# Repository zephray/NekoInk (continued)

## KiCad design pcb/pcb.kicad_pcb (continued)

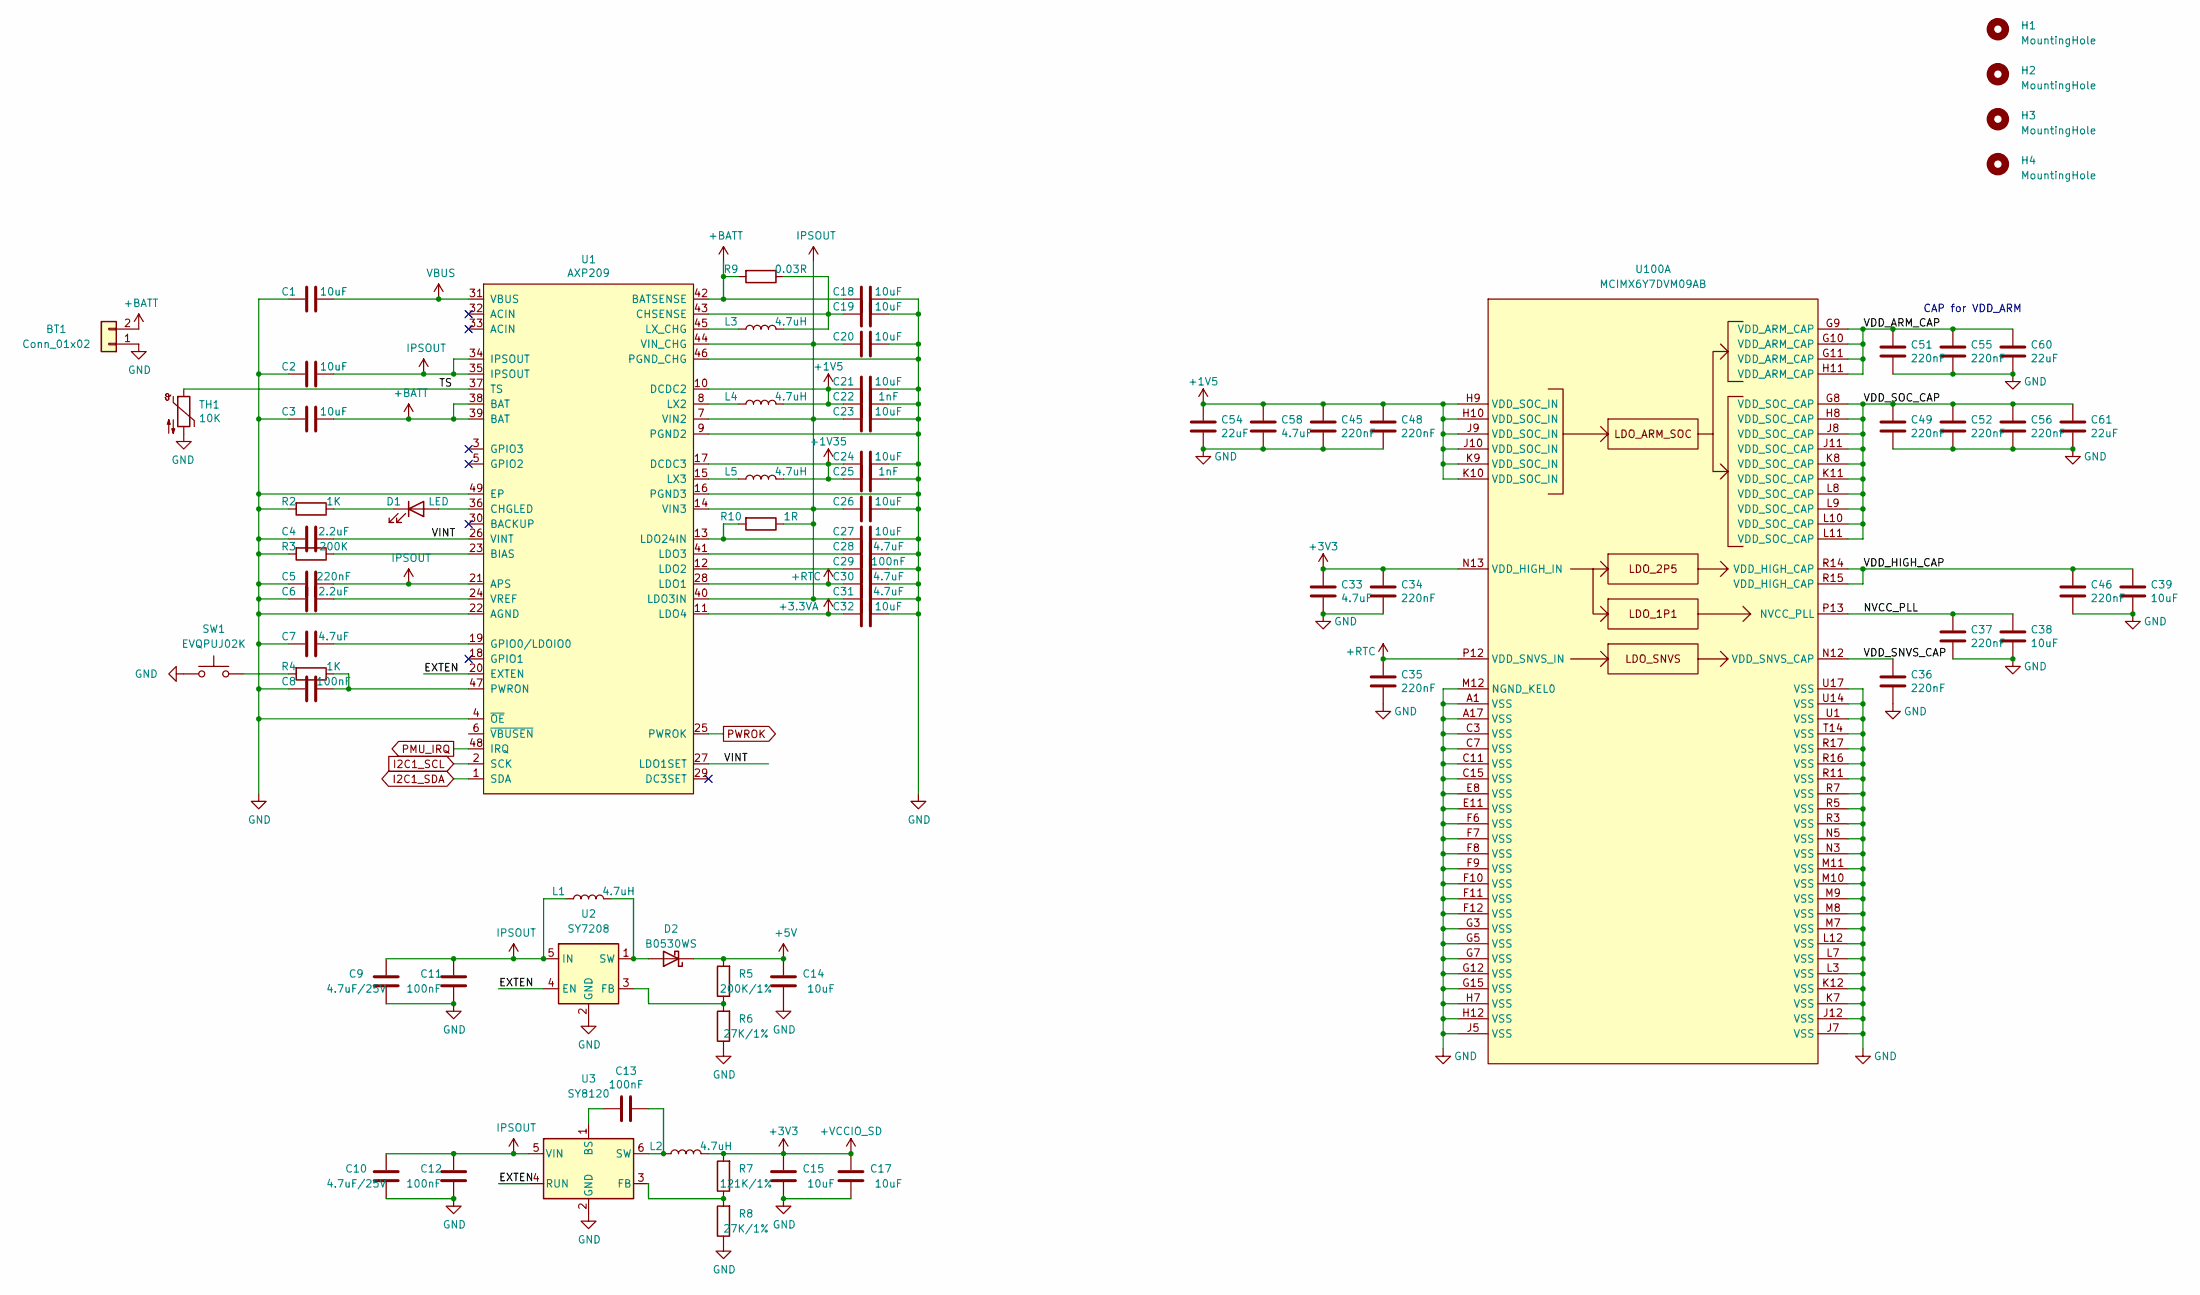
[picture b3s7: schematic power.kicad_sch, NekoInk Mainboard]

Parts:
BT1: Conn_01x02; Molex_PicoBlade_53261-0271_1x02-1MP_P1.25mm_Horizontal
C1, C2, C3, C14, C15, C17, C18, C19, C20, C21, C23, C24, C26, C27, C32, C38, C39: 10uF; C_0603_1608Metric
C4, C6: 2.2uF; C_0402_1005Metric
C5, C34, C35, C36, C37, C45, C46, C48, C49, C51, C52, C55, C56: 220nF; C_0402_1005Metric
C7, C28, C30, C31, C33, C58: 4.7uF; C_0603_1608Metric
C8, C11, C12, C13, C29: 100nF; C_0402_1005Metric
C9, C10: 4.7uF/25V; C_0805_2012Metric
C22, C25: 1nF; C_0402_1005Metric
C54, C60, C61: 22uF; C_0603_1608Metric
D1: LED; D_0603_1608Metric
D2: B0530WS; D_SOD-323
H1, H2, H3, H4: MountingHole; MountingHole_2.2mm_M2_DIN965
L1, L2, L3, L4, L5: 4.7uH; L_1212
R2, R4: 1K; R_0402_1005Metric
R3: 200K; R_0402_1005Metric
R5: 200K/1%; R_0402_1005Metric
R6, R8: 27K/1%; R_0402_1005Metric
R7: 121K/1%; R_0402_1005Metric
R9: 0.03R; R_0805_2012Metric
R10: 1R; R_0603_1608Metric
SW1: EVQPUJ02K; Panasonic_EVQPUJ_EVQPUA
TH1: 10K; R_0603_1608Metric
U1: AXP209; QFN-48-1EP_6x6mm_P0.4mm_EP4.2x4.2mm_ThermalVias
U2: SY7208; SOT-23-6
U3: SY8120; TSOT-23-6
U100: MCIMX6Y7DVM09AB; BGA-289_17x17_14.0x14.0mm

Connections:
+1V5: C21.2, C22.2, C45.1, C48.1, C54.1, C58.1, L4.2, U1.10 (DCDC2), U100.H9 (VDD_SOC_IN), U100.H10 (VDD_SOC_IN), U100.J9 (VDD_SOC_IN), U100.J10 (VDD_SOC_IN), U100.K9 (VDD_SOC_IN), U100.K10 (VDD_SOC_IN)
+1V35: C24.2, C25.2, L5.2, U1.17 (DCDC3); also elsewhere on the board
+3.3VA: C32.2, U1.11 (LDO4)
+5V: C14.2, D2.1 (K), R5.2; also elsewhere on the board
+BATT: BT1.2, C3.1, C18.2, R9.2, U1.38 (BAT), U1.39 (BAT), U1.42 (BATSENSE)
+RTC: C30.2, C35.1, U1.28 (LDO1), U100.P12 (VDD_SNVS_IN); also elsewhere on the board
/power/EXTEN: U1.20 (EXTEN), U2.4 (EN), U3.4 (RUN)
/power/NVCC_PLL: C37.1, C38.1, U100.P13 (NVCC_PLL)
/power/TS: TH1.1, U1.37 (TS)
/power/VDD_ARM_CAP: C51.1, C55.1, C60.1, U100.G9 (VDD_ARM_CAP), U100.G10 (VDD_ARM_CAP), U100.G11 (VDD_ARM_CAP), U100.H11 (VDD_ARM_CAP)
/power/VDD_HIGH_CAP: C39.1, C46.1, U100.R14 (VDD_HIGH_CAP), U100.R15 (VDD_HIGH_CAP)
/power/VDD_SNVS_CAP: C36.1, U100.N12 (VDD_SNVS_CAP)
/power/VDD_SOC_CAP: C49.1, C52.1, C56.1, C61.1, U100.G8 (VDD_SOC_CAP), U100.H8 (VDD_SOC_CAP), U100.J8 (VDD_SOC_CAP), U100.J11 (VDD_SOC_CAP), U100.K8 (VDD_SOC_CAP), U100.K11 (VDD_SOC_CAP), U100.L8 (VDD_SOC_CAP), U100.L9 (VDD_SOC_CAP), U100.L10 (VDD_SOC_CAP), U100.L11 (VDD_SOC_CAP)
/power/VINT: C4.1, U1.26 (VINT), U1.27 (LDO1SET)
GND: BT1.1, C1.2, C2.2, C3.2, C4.2, C5.2, C6.2, C7.2, C8.2, C9.1, C10.1, C11.1, C12.1, C14.1, C15.1, C17.1, C18.1, C19.1, C20.1, C21.1, C22.1, C23.1, C24.1, C25.1, C26.1, C27.1, C28.1, C29.1, C30.1, C31.1, C32.1, C33.2, C34.2, C35.2, C36.2, C37.2, C38.2, C39.2, C45.2, C46.2, C48.2, C49.2, C51.2, C52.2, C54.2, C55.2, C56.2, C58.2, C60.2, C61.2, R2.2, R3.2, R6.1, R8.1, SW1.2, TH1.2, U1.4 (~OE), U1.9 (PGND2), U1.16 (PGND3), U1.22 (AGND), U1.46 (PGND_CHG), U1.49 (EP), U2.2 (GND), U3.2 (GND), U100.A1 (VSS), U100.A17 (VSS), U100.C3 (VSS), U100.C7 (VSS), U100.C11 (VSS), U100.C15 (VSS), U100.E8 (VSS), U100.E11 (VSS), U100.F6 (VSS), U100.F7 (VSS), U100.F8 (VSS), U100.F9 (VSS), U100.F10 (VSS), U100.F11 (VSS), U100.F12 (VSS), U100.G3 (VSS), U100.G5 (VSS), U100.G7 (VSS), U100.G12 (VSS), U100.G15 (VSS), U100.H7 (VSS), U100.H12 (VSS), U100.J5 (VSS), U100.J7 (VSS), U100.J12 (VSS), U100.K7 (VSS), U100.K12 (VSS), U100.L3 (VSS), U100.L7 (VSS), U100.L12 (VSS), U100.M7 (VSS), U100.M8 (VSS), U100.M9 (VSS), U100.M10 (VSS), U100.M11 (VSS), U100.M12 (NGND_KEL0), U100.N3 (VSS), U100.N5 (VSS), U100.R3 (VSS), U100.R5 (VSS), U100.R7 (VSS), U100.R11 (VSS), U100.R16 (VSS), U100.R17 (VSS), U100.T14 (VSS), U100.U1 (VSS), U100.U14 (VSS), U100.U17 (VSS); also elsewhere on the board
I2C1_SCL: U1.2 (SCK); also elsewhere on the board
I2C1_SDA: U1.1 (SDA); also elsewhere on the board
IPSOUT: C2.1, C5.1, C9.2, C10.2, C11.2, C12.2, C20.2, C23.2, C26.2, C31.2, L1.1, R10.1, U1.7 (VIN2), U1.14 (VIN3), U1.21 (APS), U1.34 (IPSOUT), U1.35 (IPSOUT), U1.40 (LDO3IN), U1.44 (VIN_CHG), U2.5 (IN), U3.5 (VIN); also elsewhere on the board
unnamed: C6.1, U1.24 (VREF)
unnamed: C7.1, U1.19 (GPIO0/LDOIO0)
unnamed: C8.1, R4.1, U1.47 (PWRON)
unnamed: C13.1, L2.1, U3.6 (SW)
unnamed: C13.2, U3.1 (BS)
unnamed: C19.2, L3.2, R9.1, U1.43 (CHSENSE)
unnamed: C27.2, R10.2, U1.13 (LDO24IN)
unnamed: C28.2, U1.41 (LDO3)
unnamed: C29.2, U1.12 (LDO2)
unnamed: D1.1 (K), R2.1
unnamed: D1.2 (A), U1.36 (CHGLED)
unnamed: D2.2 (A), L1.2, U2.1 (SW)
unnamed: L3.1, U1.45 (LX_CHG)
unnamed: L4.1, U1.8 (LX2)
unnamed: L5.1, U1.15 (LX3)
unnamed: R3.1, U1.23 (BIAS)
unnamed: R4.2, SW1.1
unnamed: R5.1, R6.2, U2.3 (FB)
unnamed: R7.1, R8.2, U3.3 (FB)
PWROK: U1.25 (PWROK); also elsewhere on the board
VBUS: C1.1, U1.31 (VBUS); also elsewhere on the board

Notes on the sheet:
CAP for VDD_ARM

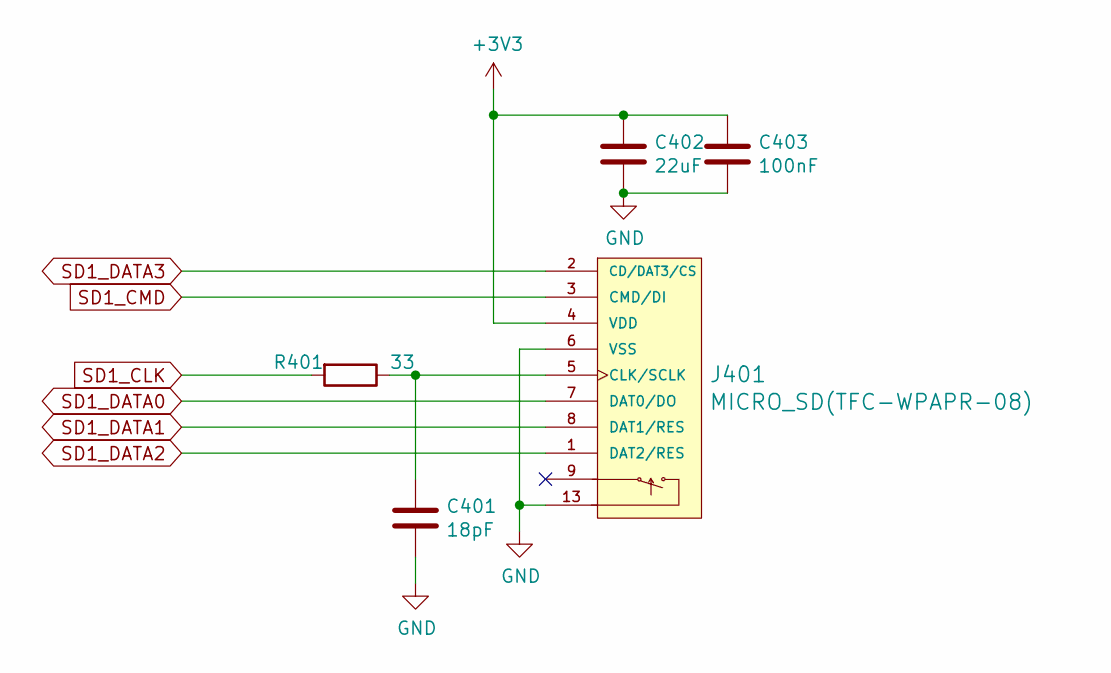
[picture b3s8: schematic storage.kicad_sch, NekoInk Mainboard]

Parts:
C401: 18pF; C_0402_1005Metric
C402: 22uF; C_0603_1608Metric
C403: 100nF; C_0402_1005Metric
J401: MICRO_SD(TFC-WPAPR-08); TFC-WPAPR-08
R401: 33; R_0402_1005Metric

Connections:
GND: C401.2, C402.2, C403.2, J401.6 (VSS), J401.10, J401.11, J401.12, J401.13; also elsewhere on the board
unnamed: C401.1, J401.5 (CLK/SCLK), R401.1
SD1_CLK: R401.2; also elsewhere on the board
SD1_CMD: J401.3 (CMD/DI); also elsewhere on the board
SD1_DATA0: J401.7 (DAT0/DO); also elsewhere on the board
SD1_DATA1: J401.8 (DAT1/RES); also elsewhere on the board
SD1_DATA2: J401.1 (DAT2/RES); also elsewhere on the board
SD1_DATA3: J401.2 (CD/DAT3/CS); also elsewhere on the board

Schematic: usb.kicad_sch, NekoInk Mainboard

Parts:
C601, C602: 10uF/25V; C_0805_2012Metric
C613, C615: 100nF; C_0402_1005Metric
J601: USB_AB_Micro; USB_Micro-AB_Molex_47590-0001
J602, J604: USB_B_Micro; USB_Micro-B_Amphenol_10103594-0001LF_Horizontal
L601, L602: EXC14CE900U; L_CommonModeChoke_Panasonic_EXC14CE
L603, L604: 120R; L_0603_1608Metric
R606, R607: 22; R_0402_1005Metric
U601, U605: USBLC6-2P6; SOT-666
U602: CP2102N-Axx-xQFN20; SiliconLabs_QFN-20-1EP_3x3mm_P0.5mm_EP1.8x1.8mm

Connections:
+5V: C601.1, L603.1; also elsewhere on the board
/usb/DEVICE_DN: J602.2 (D-), L601.4, U605.1 (I/O1), U605.6 (I/O1)
/usb/DEVICE_DP: J602.3 (D+), L601.3, U605.3 (I/O2), U605.4 (I/O2)
/usb/HOST_DN: J601.2 (D-), L602.3, U601.1 (I/O1), U601.6 (I/O1)
/usb/HOST_DP: J601.3 (D+), L602.4, U601.3 (I/O2), U601.4 (I/O2)
GND: C601.2, C602.2, C613.2, C615.2, J601.4 (ID), J601.5 (GND), J601.6 (Shield), J602.4 (ID), J602.5 (GND), J602.6 (Shield), J604.4 (ID), J604.5 (GND), J604.6 (Shield), U601.2 (GND), U602.3 (GND), U602.12 (GND), U602.21 (GND), U605.2 (GND); also elsewhere on the board
unnamed: C613.1, C615.1, U602.6 (VDD)
unnamed: J601.1 (VBUS), L603.2, U601.5 (VBUS)
unnamed: J602.1 (VBUS), L604.2, U605.5 (VBUS)
unnamed: J604.1 (VBUS), U602.7 (VREGIN), U602.8 (VBUS)
unnamed: J604.2 (D-), R607.1
unnamed: J604.3 (D+), R606.1
unnamed: R606.2, U602.4 (D+)
unnamed: R607.2, U602.5 (D-)
UART3_RXD: U602.18 (TXD); also elsewhere on the board
UART3_TXD: U602.17 (RXD); also elsewhere on the board
USB_DEVICE_DN: L601.1; also elsewhere on the board
USB_DEVICE_DP: L601.2; also elsewhere on the board
USB_HOST_DN: L602.2; also elsewhere on the board
USB_HOST_DP: L602.1; also elsewhere on the board
VBUS: C602.1, L604.1; also elsewhere on the board

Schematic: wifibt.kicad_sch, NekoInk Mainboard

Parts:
ANT901: PCB_WIFI_ANT; bt_antenna_1ant_2gnd
C901, C902: DNP; C_0402_1005Metric
C903: 33pF/50V/5%; C_0402_1005Metric
C904, C906: 100nF; C_0402_1005Metric
C905, C907: 10uF; C_0603_1608Metric
R901: 0R; R_0402_1005Metric
R902: 10K; R_0402_1005Metric
U901: RTL8723BS; RL-SM02BD(RTL8723BS)
X901: 32.768kHz; Oscillator_SMD_Abracon_ASE-4Pin_3.2x2.5mm

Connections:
GND: ANT901.2, C901.1, C902.1, C904.2, C905.2, C906.2, C907.2, U901.1 (GND), U901.20 (GND), U901.31 (GND), U901.33 (GND), U901.36 (GND), X901.2 (GND); also elsewhere on the board
unnamed: ANT901.1, C901.2, R901.2
unnamed: C902.2, C903.2, R901.1
unnamed: C903.1, U901.2 (WIFI/BT_ANT)
unnamed: R902.2, X901.1 (EN)
unnamed: U901.24 (SUSCLK_IN/GPIO6), X901.3 (OUT)
SD2_CLK: U901.17 (SD_CLK); also elsewhere on the board
SD2_CMD: U901.16 (SD_CMD); also elsewhere on the board
SD2_DATA0: U901.18 (SD_D0); also elsewhere on the board
SD2_DATA1: U901.19 (SD_D1); also elsewhere on the board
SD2_DATA2: U901.14 (SD_D2); also elsewhere on the board
SD2_DATA3: U901.15 (SD_D3); also elsewhere on the board
UART2_CTS: U901.41 (UART_RTS); also elsewhere on the board
UART2_RTS: U901.44 (UART_CTS); also elsewhere on the board
UART2_RXD: U901.42 (UART_OUT); also elsewhere on the board
UART2_TXD: U901.43 (UART_IN); also elsewhere on the board
WL_PMU_EN: U901.12 (WL_DIS#/GPIO9); also elsewhere on the board
WL_WAKE_AP: U901.13 (WL_HOST_WAKE); also elsewhere on the board

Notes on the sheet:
Headset profile is not supported. Use A2DP instead.

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
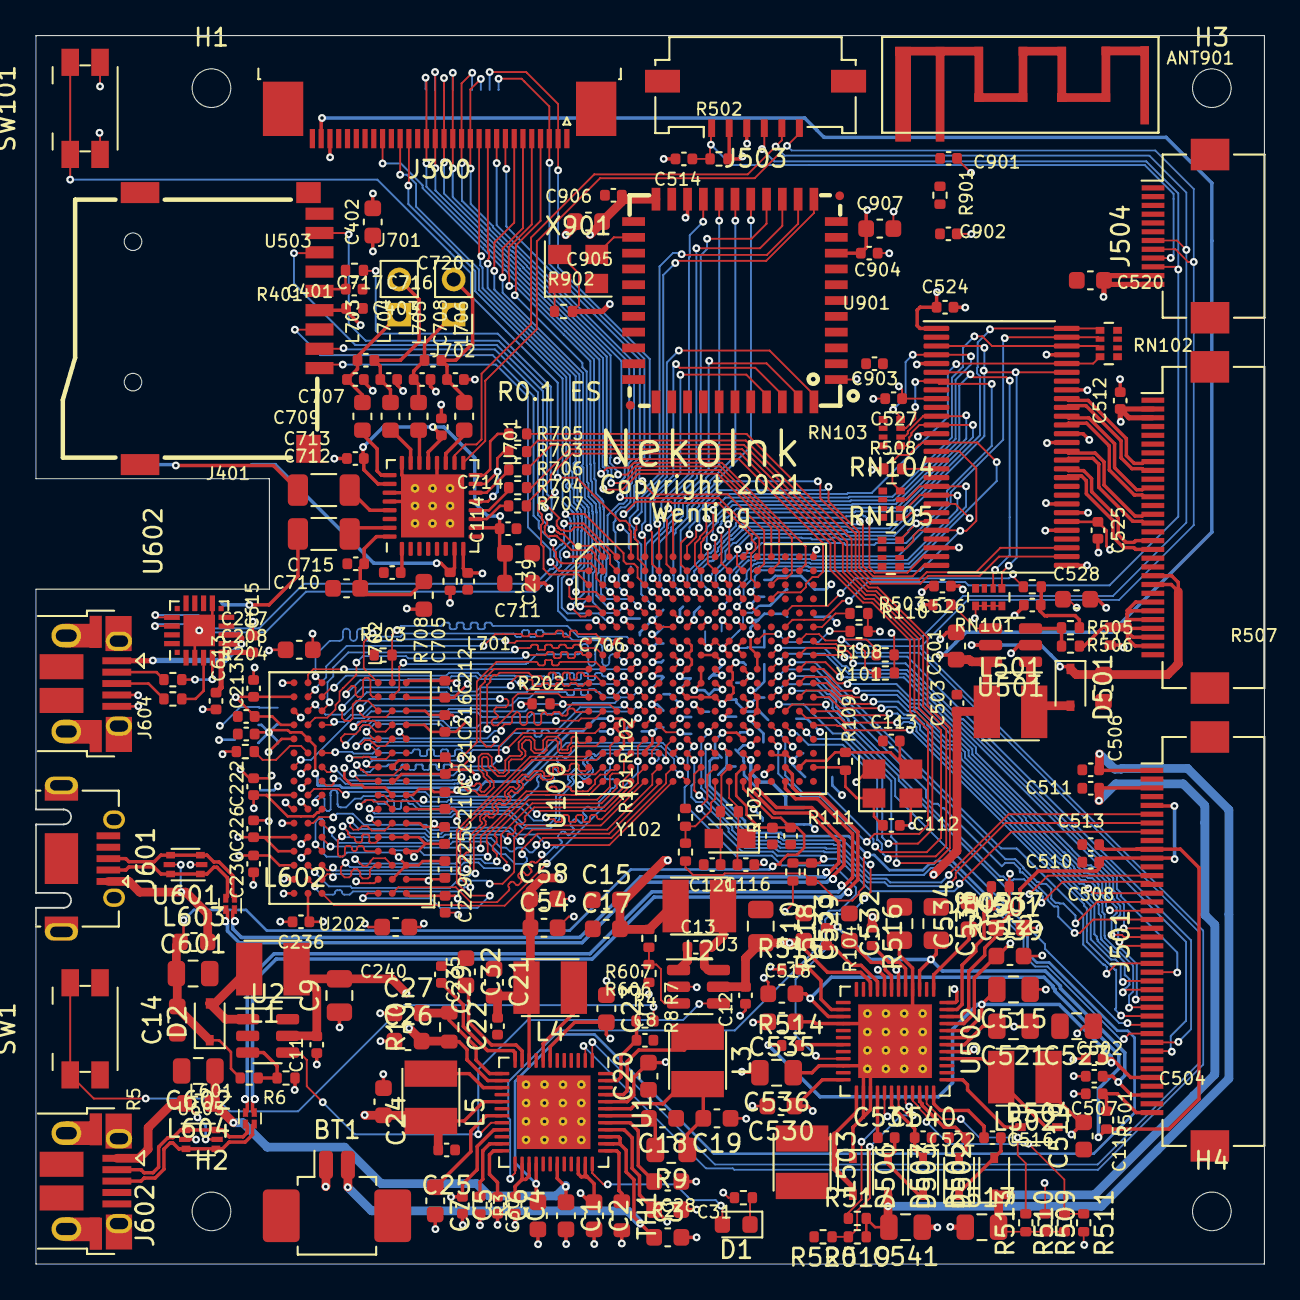
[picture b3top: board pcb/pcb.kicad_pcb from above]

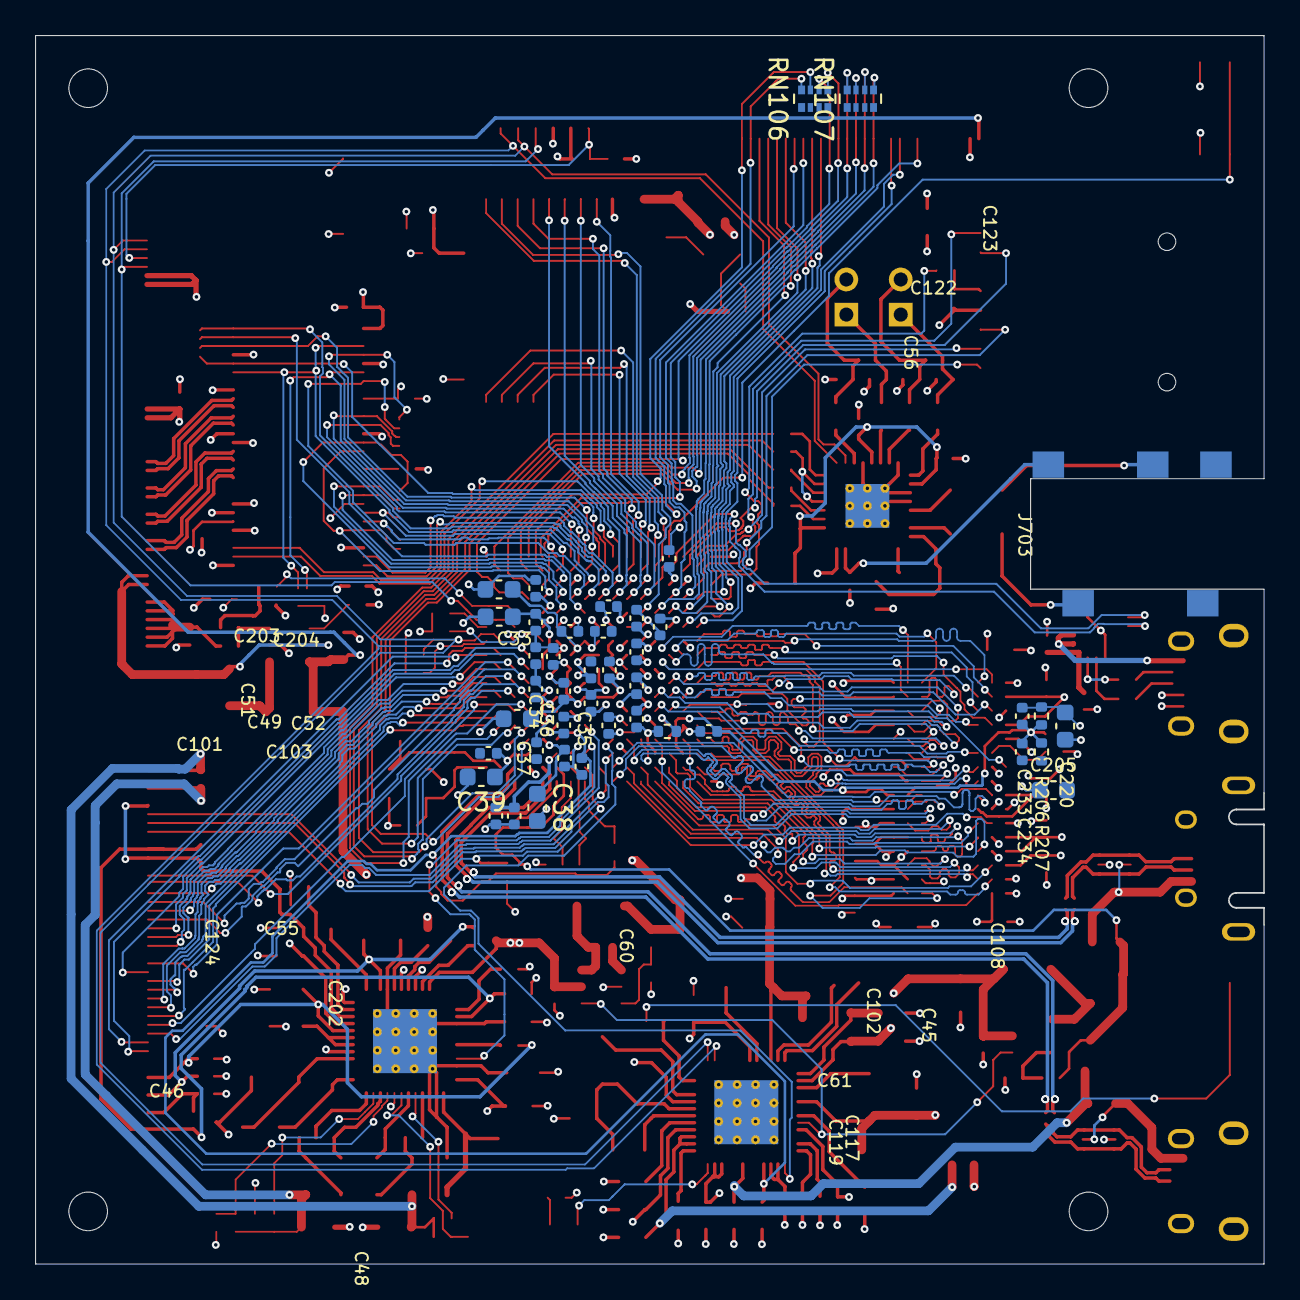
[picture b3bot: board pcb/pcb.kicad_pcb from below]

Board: 4 copper layers, 70.0 x 70.0 mm, 289 parts (42 on the bottom side), 275 nets.

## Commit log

2021-09-03 license and readme
2021-09-03 pcb: r0p1 wip
2021-09-05 pcb: finish routing r0p1
2021-09-06 pcb: revise r0p1 design, ready for production
2021-09-10 utils: waveform assembler wip
2021-09-12 utils: initial waveform assembler for imx6/7 epdc
2021-09-12 waveform: add raw waveform for gdew101
2021-09-13 utils: initial imgview utility
2021-09-14 utils: doc waveform related info
2021-09-15 utils: implement color dithering and other improvements
2021-09-18 - Working on removing SDL dependency for target platform use
2021-09-18 - Add license for utils provided in README
2021-09-18 - Preparing for actual hardware target - Use LUT for gamma correction
2021-09-18 utils: add spreadsheet for timing calculation
2021-09-19 utils: fix memory issues in waveform asm
2021-09-21 utils: new fw dump tool; support for v2 epdc format; new iwf allows different table length for different temperatures
2021-09-23 utils: imgview working on target
2021-10-03 pcb: getting ready for r0.2 production
2021-10-16 pcb: move mb to its own directory
2021-10-18 pcb: switch to max17135, length tuning for QSPI and SD
2021-11-14 pcb: mainboard r0.2 freeze
2022-03-05 - Update to KiCad 6.0 - Fix MT41K256M16 symbol missing pin in library
2022-03-26 utils: sepearate Makefile for target and PC
2022-04-03 utils: change optimization level down for PC build
2022-05-28 pcb: adapter for 39p/50p screens
2022-05-29 pcb: adapter for 34p screens
2022-06-14 util: fix dithering for color panel; implement blue noise and ordered dithering
2023-03-24 Triton 2 color support
2023-07-02 Rename pcb/mainboard to pcb/mainboard_gen1
2023-07-02 Add adapter board for 35pin connector
2023-12-27 Revert "Triton 2 color support"
    This reverts commit 02d3daa51657f19f5df007baddab4ebbc355173f.
2024-01-01 Implement 4bpp/5bpp wbf import tool
2024-01-02 Add waveform mode labeling in the wbf extractor
2024-01-03 Experimental support for 4bit packing in wbf
2024-01-14 Shelved Gen2 board design
2024-01-14 Fix gamma aware dithering
2024-01-14 Add decompressing tool
2024-05-13 Deprecation notice
